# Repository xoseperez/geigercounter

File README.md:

# Geiger Counter

Geiger counter based on the [Geiger Counter Radiation Detector DIY Kit](http://www.rhelectronics.net/store/radiation-detector-geiger-counter-diy-kit-second-edition.html "Geiger Counter Radiation Detector DIY Kit") from [Radio Hobby Store](http://www.rhelectronics.net/store/ "RH electronics store").

You can read about this project in my blog: [Geiger Counter](http://tinkerman.eldiariblau.net/geiger-counter/ "Geiger Counter").

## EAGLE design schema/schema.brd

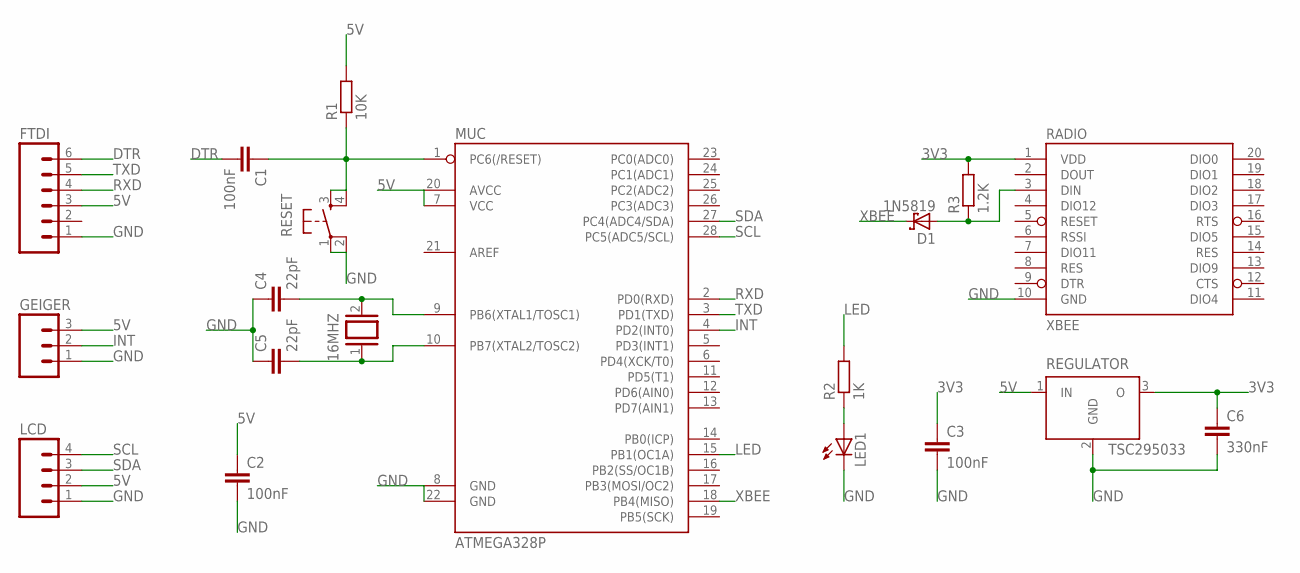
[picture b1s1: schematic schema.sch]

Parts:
16MHZ: XTAL/S; QS
C1, C2, C3: 100nF; C025-025X050
C4, C5: 22pF; C025-025X050
C6: 330nF; C025-025X050
D1: 1N5819; DO41-7.6
FTDI: M06SIP; 1X06
GEIGER: M03PTH; 1X03
LCD: M04PTH; 1X04
LED1: LED3MM
MUC: ATMEGA328P; DIL28-3
R1: 10K; 0207/10
R2: 1K; 0207/10
R3: 1.2K; 0207/10
RADIO: XBEE; XBEE-1
REGULATOR: TSC295033; TO92
RESET: TAC_SWITCHPTH; TACTILE-PTH

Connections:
3V3: C3.1, C6.1, R3.2, RADIO.1 (VDD), REGULATOR.3 (O)
5V: C2.1, FTDI.3, GEIGER.3, LCD.2, MUC.7 (VCC), MUC.20 (AVCC), R1.2, REGULATOR.1 (IN)
DTR: C1.2, FTDI.6
GND: C2.2, C3.2, C4.1, C5.1, C6.2, FTDI.1, GEIGER.1, LCD.1, LED1.K (C), MUC.8 (GND), MUC.22 (GND), RADIO.10 (GND), REGULATOR.2 (GND), RESET.1, RESET.2
INT: GEIGER.2, MUC.4 (PD2(INT0))
LED: MUC.15 (PB1(OC1A)), R2.2
unnamed: C1.1, MUC.1 (PC6(/RESET)), R1.1, RESET.3, RESET.4
unnamed: 16MHZ.2, C4.2, MUC.9 (PB6(XTAL1/TOSC1))
unnamed: 16MHZ.1, C5.2, MUC.10 (PB7(XTAL2/TOSC2))
unnamed: D1.A, R3.1, RADIO.3 (DIN)
unnamed: LED1.A, R2.1
RXD: FTDI.4, MUC.2 (PD0(RXD))
SCL: LCD.4, MUC.28 (PC5(ADC5/SCL))
SDA: LCD.3, MUC.27 (PC4(ADC4/SDA))
TXD: FTDI.5, MUC.3 (PD1(TXD))
XBEE: D1.C, MUC.18 (PB4(MISO))

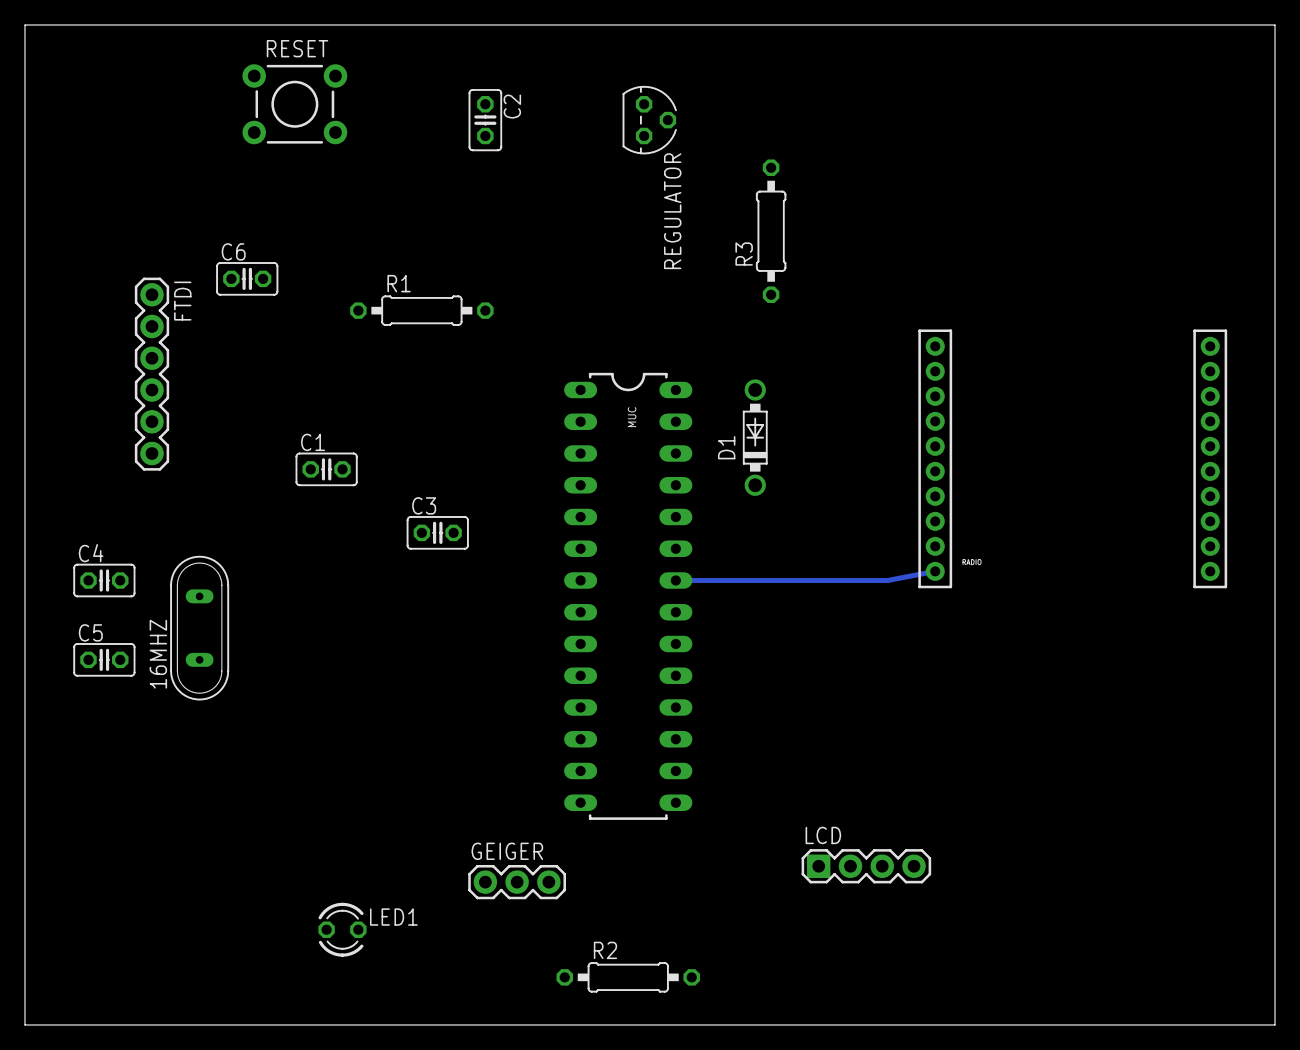
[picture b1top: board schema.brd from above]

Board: 2 copper layers, 100.0 x 80.0 mm, 19 parts (0 on the bottom side), 16 nets.

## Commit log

2013-05-08 Add Xbee support and improve LCD displaying
2013-05-08 Some refactoring
2013-05-08 Using NewLiquidCrystal library interfacing with cheapo I2C LCD module
2013-05-08 Eagle schema
2013-05-08 Small changes in the eagle schema
2013-05-10 Stripboard design and PIN changes
2013-05-10 Bug fix in the eagle schema: replace zener for schottky
2013-05-13 Fix stripboard layout
2013-05-16 Modify project to uso Ino Toolkit
2013-05-17 Fix schematics
2013-05-23 Small improvements, added comments and references
2017-04-04 Pending changes
2017-04-04 Moteino based version

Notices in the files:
parts and their libraries:
SparkFun-DigitalIC: Licensing: CC v3.0 Share-Alike You are welcome to use this library for commercial purposes.
